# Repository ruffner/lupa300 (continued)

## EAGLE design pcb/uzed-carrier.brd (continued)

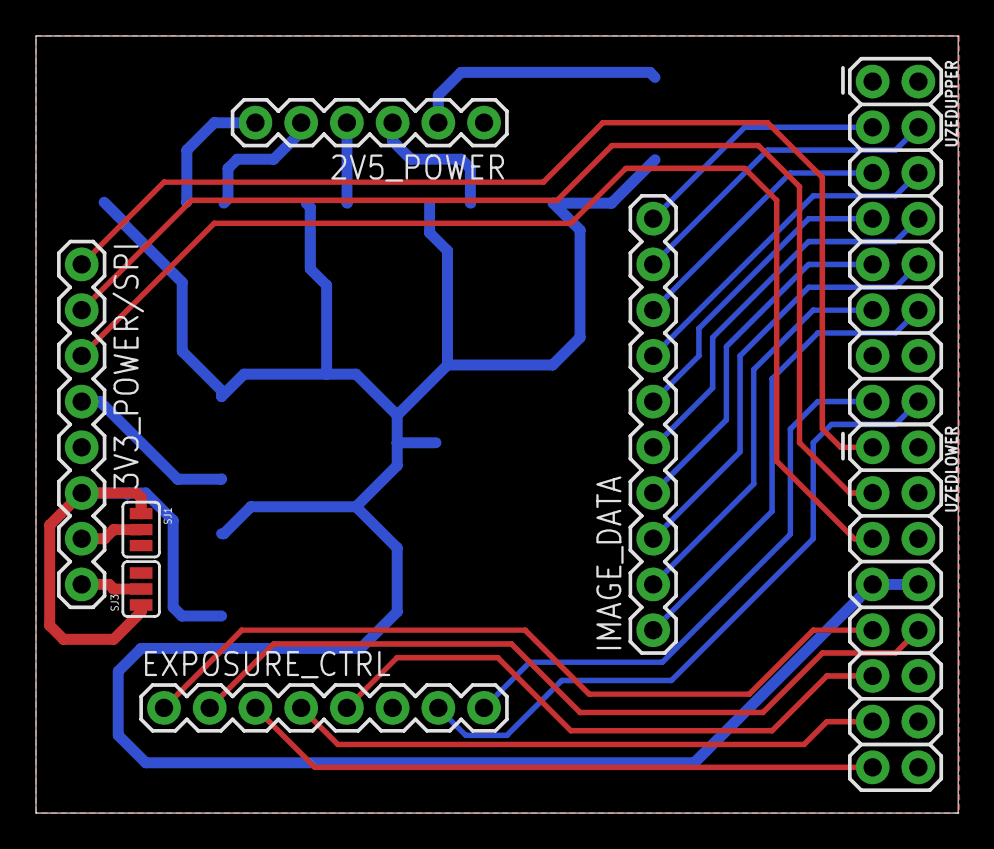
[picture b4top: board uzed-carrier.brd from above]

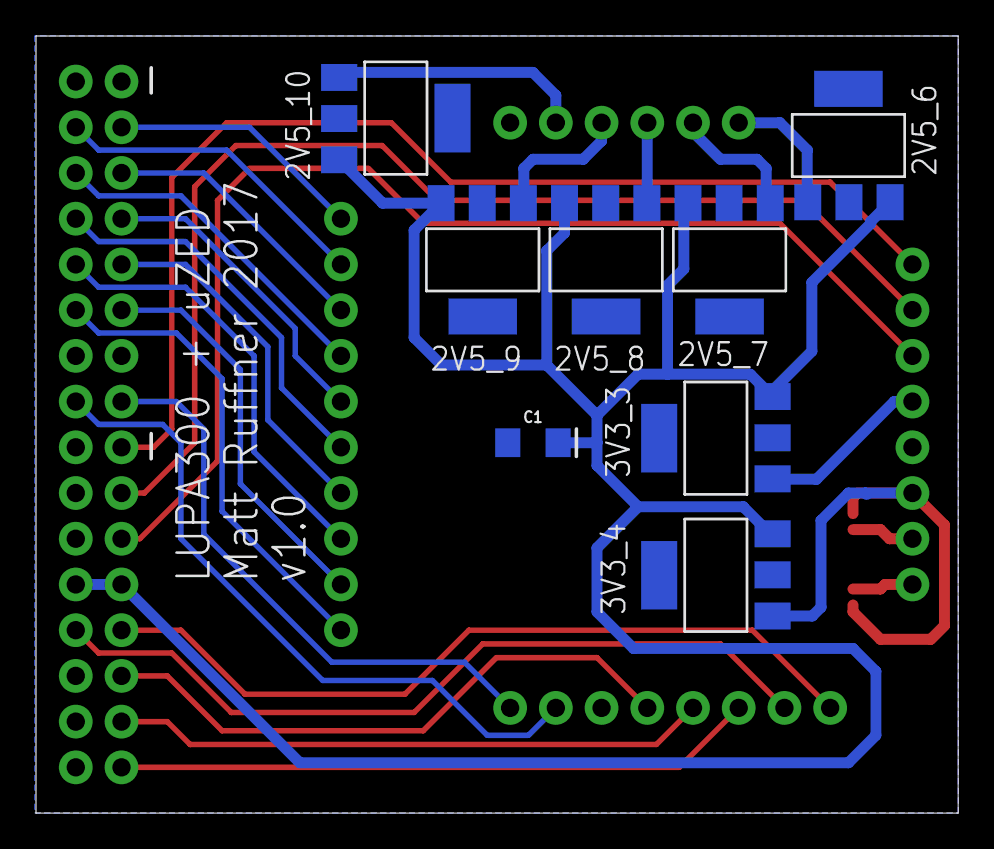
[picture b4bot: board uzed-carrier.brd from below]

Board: 2 copper layers, 51.2 x 43.2 mm, 16 parts (8 on the bottom side), 31 nets.
